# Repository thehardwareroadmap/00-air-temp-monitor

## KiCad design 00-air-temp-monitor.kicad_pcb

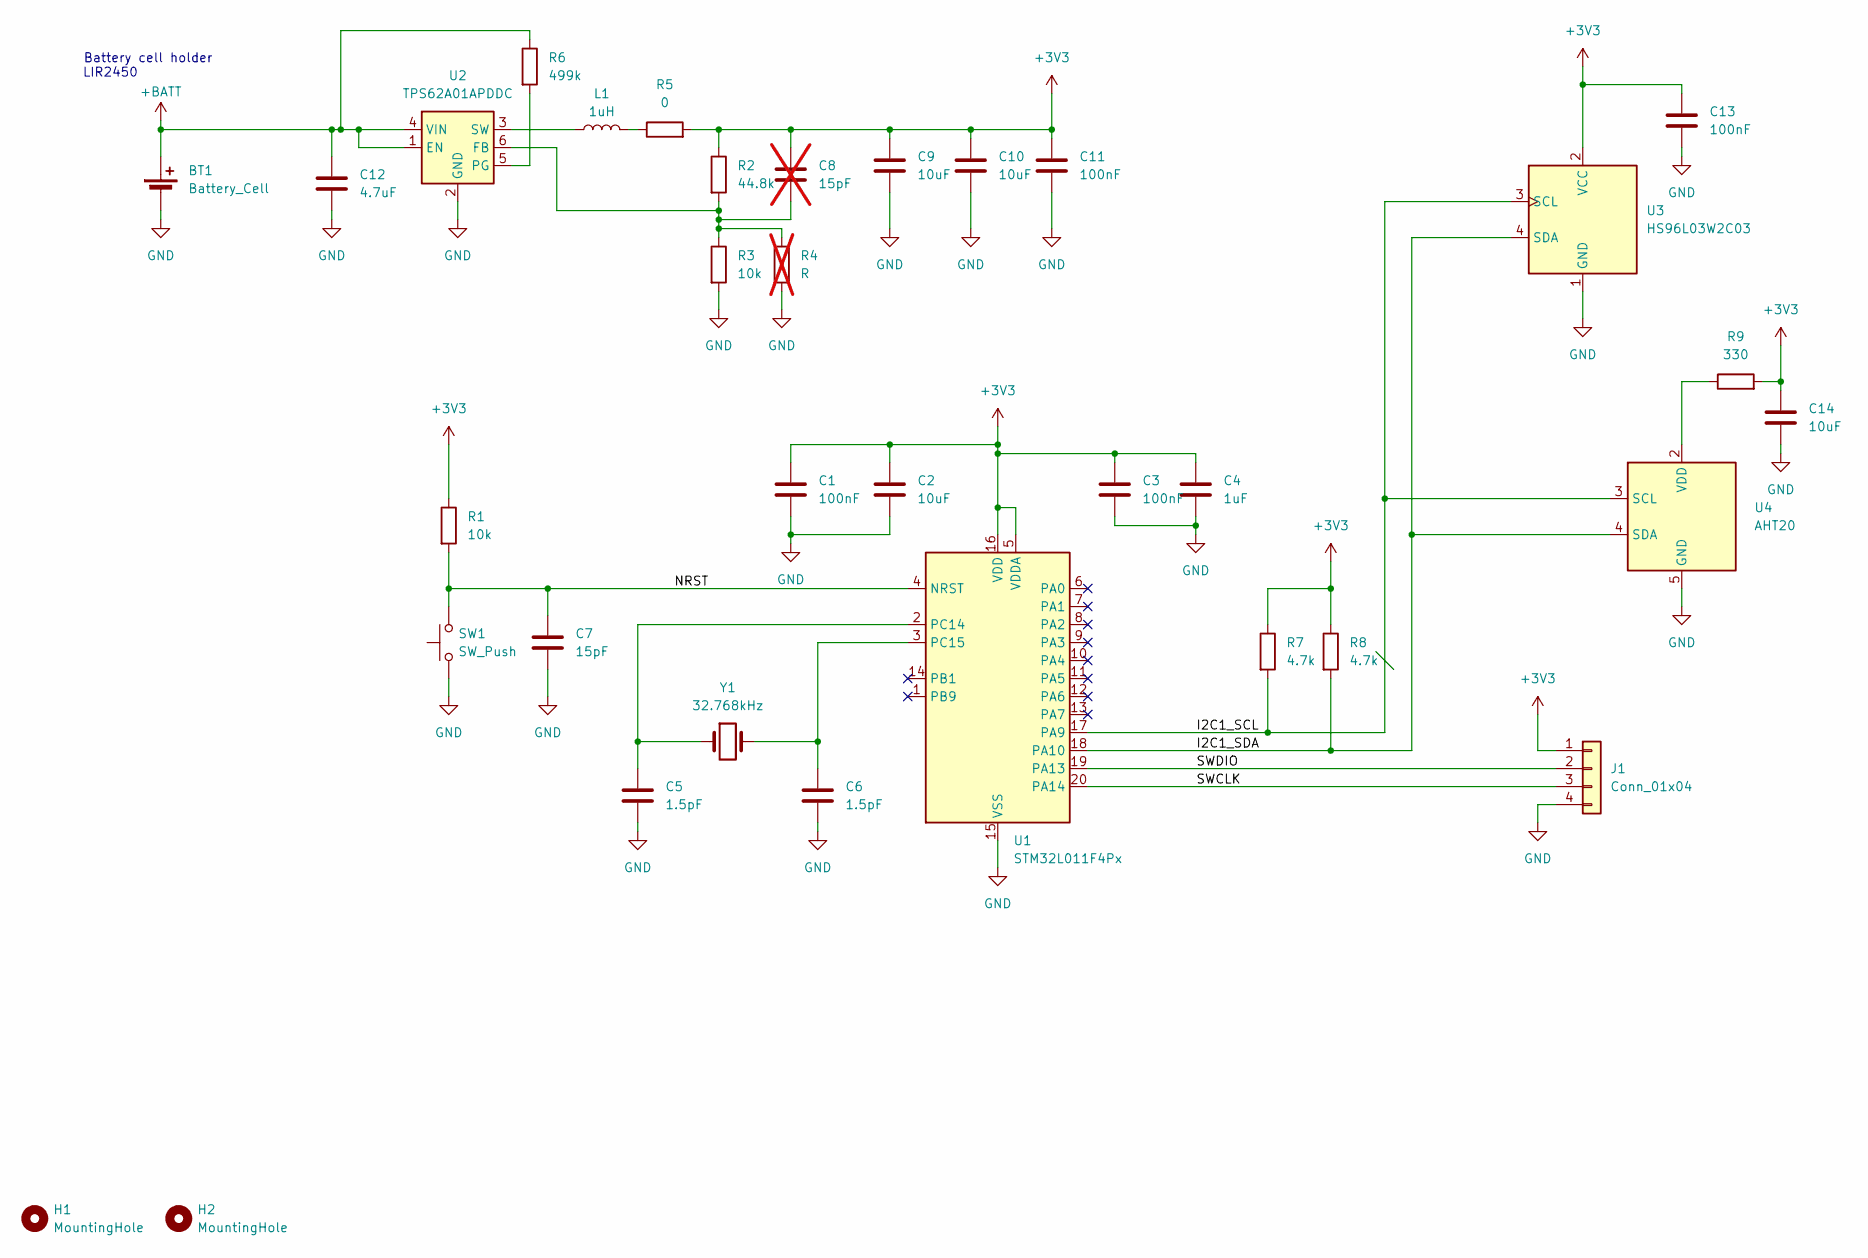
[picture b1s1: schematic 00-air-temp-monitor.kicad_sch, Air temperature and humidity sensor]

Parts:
BT1: Battery_Cell; BS-24-B4AK023; LCSC Part # C2902329
C1, C3, C11, C13: 100nF; C_0402_1005Metric_Pad0.74x0.62mm_HandSolder; LCSC Part # C2857965
C2, C9, C10, C14: 10uF; C_0402_1005Metric_Pad0.74x0.62mm_HandSolder; LCSC Part # C408132
C4: 1uF; C_0402_1005Metric_Pad0.74x0.62mm_HandSolder; LCSC Part # C14445
C5, C6: 1.5pF; C_0402_1005Metric_Pad0.74x0.62mm_HandSolder; LCSC Part # C285112
C7: 15pF; C_0402_1005Metric_Pad0.74x0.62mm_HandSolder; LCSC Part # C1548
C8: 15pF; C_0402_1005Metric_Pad0.74x0.62mm_HandSolder; LCSC Part # C1548; not fitted
C12: 4.7uF; C_0402_1005Metric_Pad0.74x0.62mm_HandSolder; LCSC Part # C20624278
H1, H2: MountingHole; MountingHole_2.7mm_M2.5
J1: Conn_01x04; PinHeader_1x04_P2.54mm_Vertical; LCSC Part # C5383113
L1: 1uH; L_1008_2520Metric_Pad1.43x2.20mm_HandSolder; LCSC Part # C435392
R1, R3: 10k; R_0402_1005Metric_Pad0.72x0.64mm_HandSolder; LCSC Part # C22356213
R2: 44.8k; R_0402_1005Metric_Pad0.72x0.64mm_HandSolder; LCSC Part # C852792
R4: R; R_0402_1005Metric_Pad0.72x0.64mm_HandSolder; not fitted
R5: 0; R_0402_1005Metric_Pad0.72x0.64mm_HandSolder; LCSC Part # C17168
R6: 499k; R_0402_1005Metric_Pad0.72x0.64mm_HandSolder; LCSC Part # C324794
R7, R8: 4.7k; R_0402_1005Metric_Pad0.72x0.64mm_HandSolder; LCSC Part # C25900
R9: 330; R_0402_1005Metric_Pad0.72x0.64mm_HandSolder; LCSC Part # C12246
SW1: SW_Push; Tactile_switch_4.5x4.5x5.0; LCSC Part # C39832245
U1: STM32L011F4Px; TSSOP-20_4.4x6.5mm_P0.65mm; LCSC Part # C87903
U2: TPS62A01APDDC; SOT-23-6; LCSC Part # C41730179
U3: HS96L03W2C03; LCSC Part # C5248080
U4: AHT20; MPN AHT20; LCSC Part # C2757850
Y1: 32.768kHz; Crystal_SMD_2012-2Pin_2.0x1.2mm_HandSoldering; LCSC Part # C276418

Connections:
+3V3: C1.1, C2.1, C3.1, C4.1, C8.1, C9.1, C10.1, C11.1, C13.1, C14.1, J1.1, R1.1, R2.1, R5.2, R7.1, R8.1, R9.2, U1.5 (VDDA), U1.16 (VDD), U3.2 (VCC)
+BATT: BT1.1 (+), C12.1, R6.1, U2.1 (EN), U2.4 (VIN)
/I2C1_SCL: R7.2, U1.17 (PA9), U3.3 (SCL), U4.3 (SCL)
/I2C1_SDA: R8.2, U1.18 (PA10), U3.4 (SDA), U4.4 (SDA)
/NRST: C7.1, R1.2, SW1.2, U1.4 (NRST)
/SWCLK: J1.3, U1.20 (PA14)
/SWDIO: J1.2, U1.19 (PA13)
GND: BT1.2 (-), C1.2, C2.2, C3.2, C4.2, C5.2, C6.2, C7.2, C9.2, C10.2, C11.2, C12.2, C13.2, C14.2, J1.4, R3.2, R4.2, SW1.1, U1.15 (VSS), U2.2 (GND), U3.1 (GND), U4.5 (GND)
unnamed: L1.2, R5.1
unnamed: C5.1, U1.2 (PC14), Y1.1
unnamed: C6.1, U1.3 (PC15), Y1.2
unnamed: C8.2, R2.2, R3.1, R4.1, U2.6 (FB)
unnamed: R6.2, U2.5 (PG)
unnamed: L1.1, U2.3 (SW)
unnamed: R9.1, U4.2 (VDD)

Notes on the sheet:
LIR2450
Battery cell holder

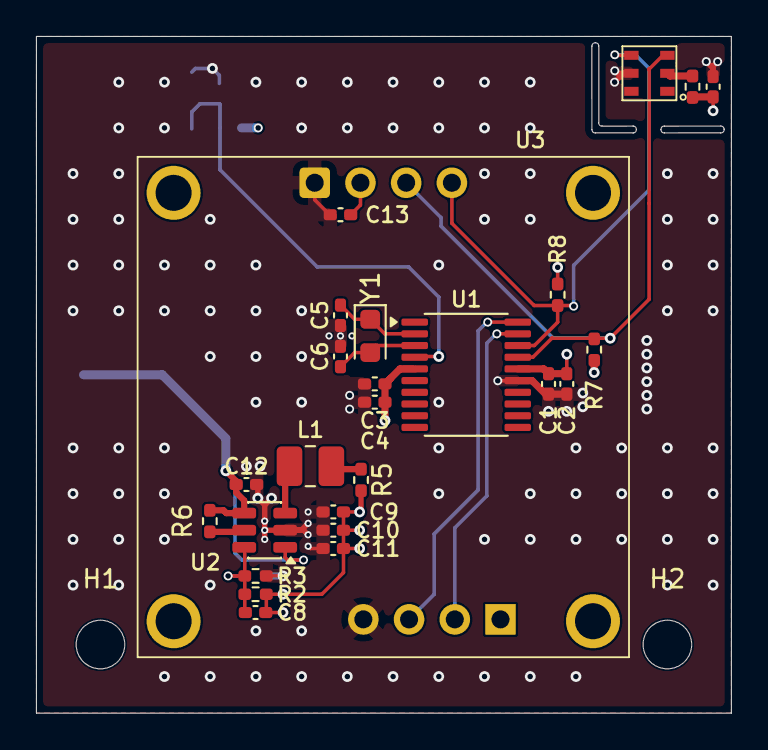
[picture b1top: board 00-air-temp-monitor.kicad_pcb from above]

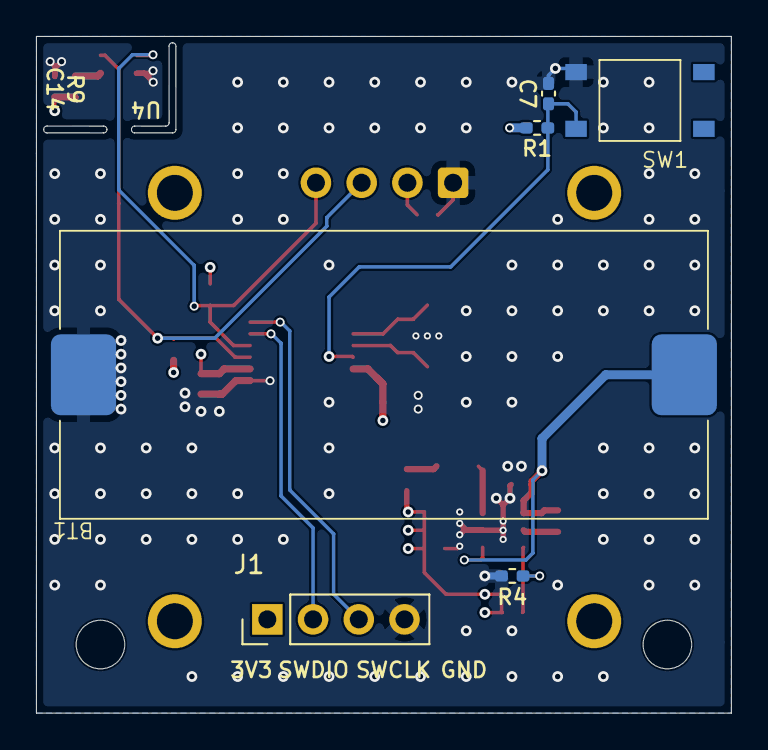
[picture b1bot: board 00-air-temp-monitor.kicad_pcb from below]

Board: 4 copper layers, 38.6 x 37.6 mm, 34 parts (6 on the bottom side), 15 nets.
